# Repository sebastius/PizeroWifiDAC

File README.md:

# PizeroWifiDAC
WiFi + DAC for Pi Zero

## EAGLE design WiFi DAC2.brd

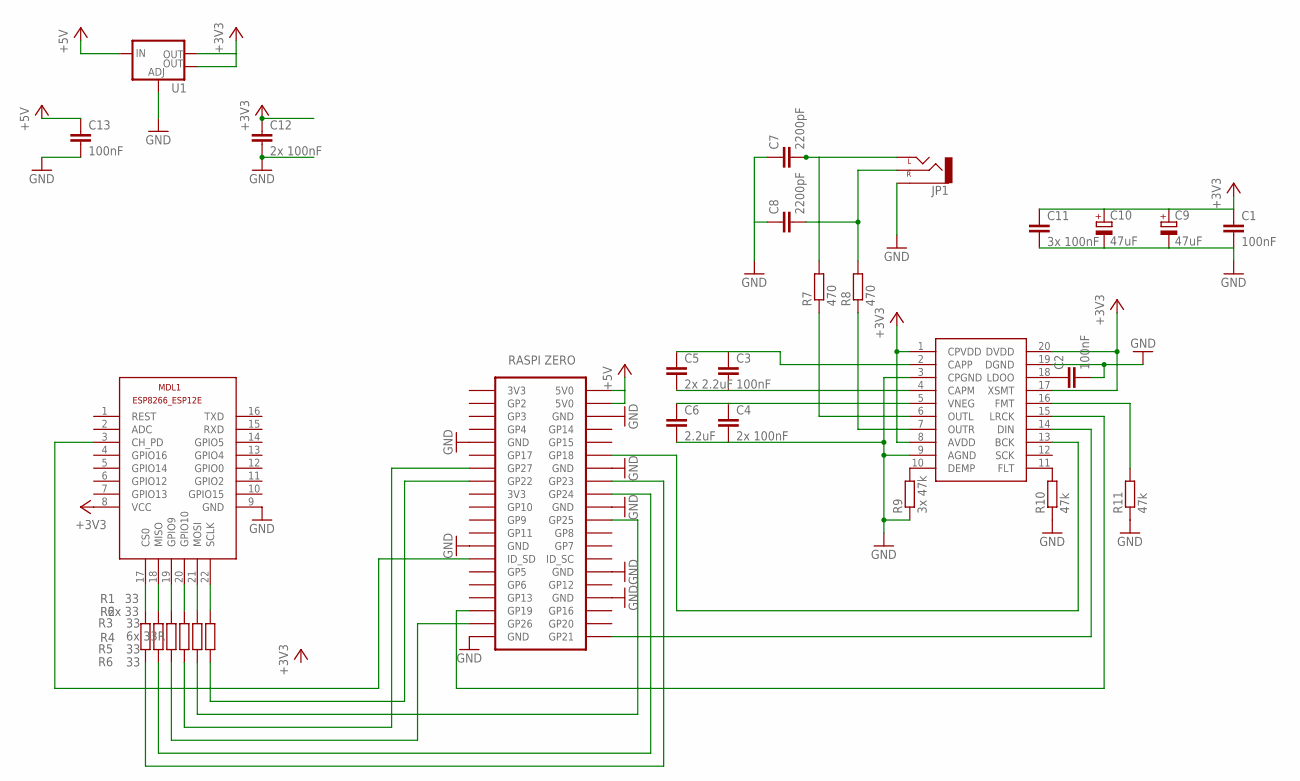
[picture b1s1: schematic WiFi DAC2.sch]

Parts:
C1, C2, C3, C13: 100nF; C0603
C4, C12: 2x 100nF; C0603
C5: 2x 2.2uF; C0603
C6: 2.2uF; C0603
C7, C8: 2200pF; C0603
C9, C10: 47uF; SANYO-OSCON_SMD_A5
C11: 3x 100nF; C0603
JP1: AUDIO-JACKPTH; AUDIO-JACK
MDL1: ESP8266-12EESP8266-ESP12E; ESP8266-ESP12E
R1, R3, R5, R6: 33; R0603
R2: 6x 33; R0603
R4: 6x 33R; R0603
R7, R8: 470; R0603
R9: 3x 47k; R0603
R10, R11: 47k; R0603
U1: V_REG_LM1117SOT223; SOT223
U$1: ZERO
U$2: PCM5102; TSSOP20

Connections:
+3V3: C1.1, C9.+, C10.+, C11.1, C12.1, MDL1.8 (VCC), U1.2 (OUT), U1.4 (OUT), U$2.1 (CPVDD), U$2.8 (AVDD), U$2.17 (XSMT), U$2.20 (DVDD)
+5V: C13.1, U1.3 (IN), U$1.2 (5V0), U$1.4 (5V0)
GND: C1.2, C2.2, C4.2, C6.2, C7.1, C8.1, C9.-, C10.-, C11.2, C12.2, C13.2, JP1.SLEEVE, MDL1.9 (GND), R9.1, R10.1, R11.1, U1.1 (ADJ), U$1.6 (GND), U$1.9 (GND), U$1.14 (GND), U$1.20 (GND), U$1.25 (GND), U$1.30 (GND), U$1.34 (GND), U$1.39 (GND), U$2.3 (CPGND), U$2.9 (AGND), U$2.19 (DGND)
unnamed: MDL1.17 (CS0), R1.2
unnamed: MDL1.18 (MISO), R2.2
unnamed: MDL1.19 (GPIO9), R3.2
unnamed: MDL1.20 (GPIO10), R4.2
unnamed: MDL1.21 (MOSI), R5.2
unnamed: MDL1.22 (SCLK), R6.2
unnamed: R1.1, U$1.16 (GP23)
unnamed: R2.1, U$1.18 (GP24)
unnamed: R3.1, U$1.37 (GP26)
unnamed: R4.1, U$1.13 (GP27)
unnamed: R5.1, U$1.22 (GP25)
unnamed: R6.1, U$1.15 (GP22)
unnamed: MDL1.3 (CH_PD), U$1.27 (ID_SD)
unnamed: U$1.35 (GP19), U$2.15 (LRCK)
unnamed: U$1.40 (GP21), U$2.14 (DIN)
unnamed: U$1.12 (GP18), U$2.13 (BCK)
unnamed: C2.1, U$2.18 (LDOO)
unnamed: C3.2, C5.2, U$2.4 (CAPM)
unnamed: C3.1, C5.1, U$2.2 (CAPP)
unnamed: C4.1, C6.1, U$2.5 (VNEG)
unnamed: C7.2, JP1.TIP (LEFT), R7.2
unnamed: C8.2, JP1.RING (RIGHT), R8.2
unnamed: R7.1, U$2.6 (OUTL)
unnamed: R8.1, U$2.7 (OUTR)
unnamed: R9.2, U$2.10 (DEMP)
unnamed: R10.2, U$2.11 (FLT)
unnamed: R11.2, U$2.16 (FMT)

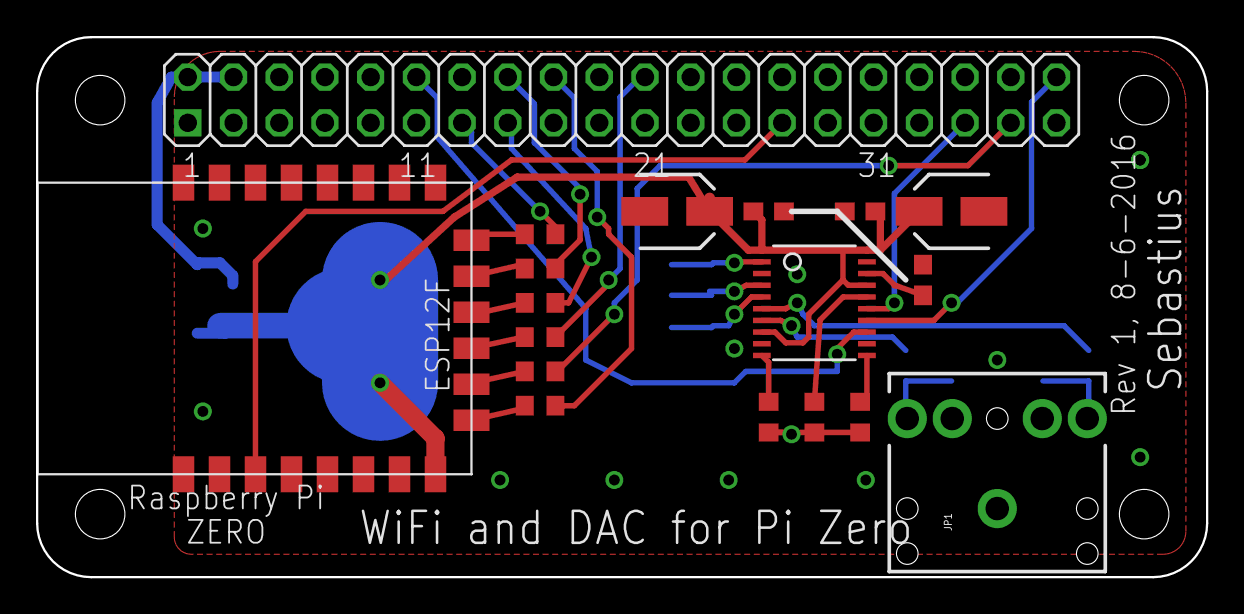
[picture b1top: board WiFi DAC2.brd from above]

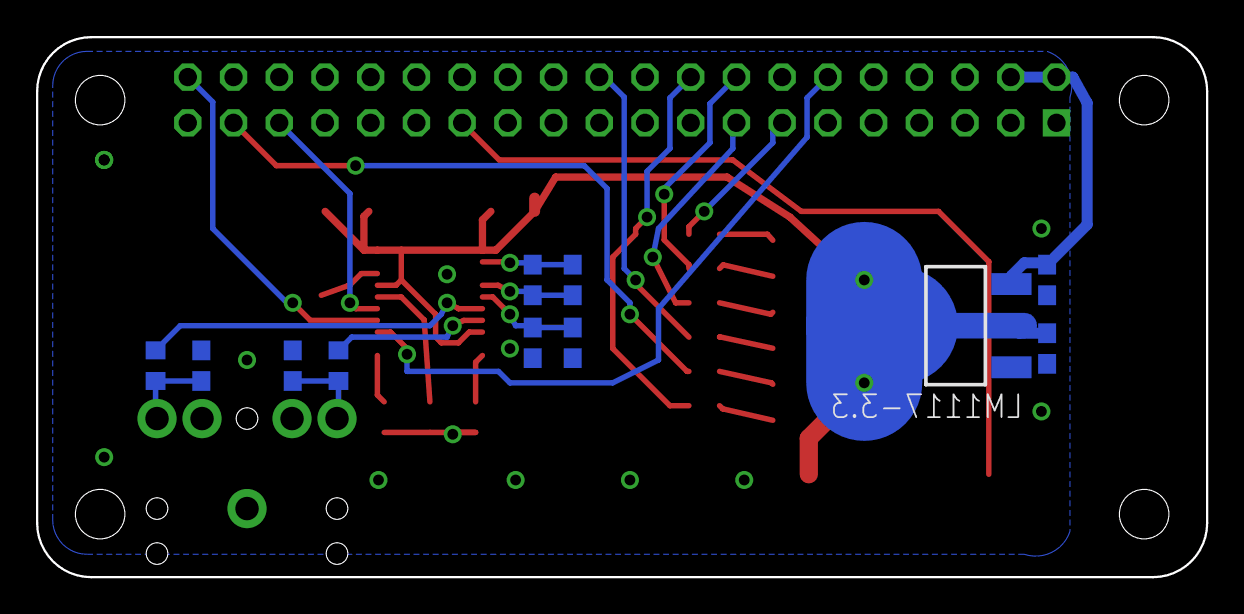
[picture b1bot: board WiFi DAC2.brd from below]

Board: 2 copper layers, 65.0 x 30.0 mm, 29 parts (11 on the bottom side), 30 nets.

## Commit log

2016-06-07 starting
2016-06-07 libraries
2016-06-07 Meer op z'n plek
2016-06-08 test
    jup

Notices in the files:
parts and their libraries:
SparkFun-PowerIC: Licensing: Creative Commons ShareAlike 4.0 International - https://creativecommons.org/licenses/by-sa/4.0
